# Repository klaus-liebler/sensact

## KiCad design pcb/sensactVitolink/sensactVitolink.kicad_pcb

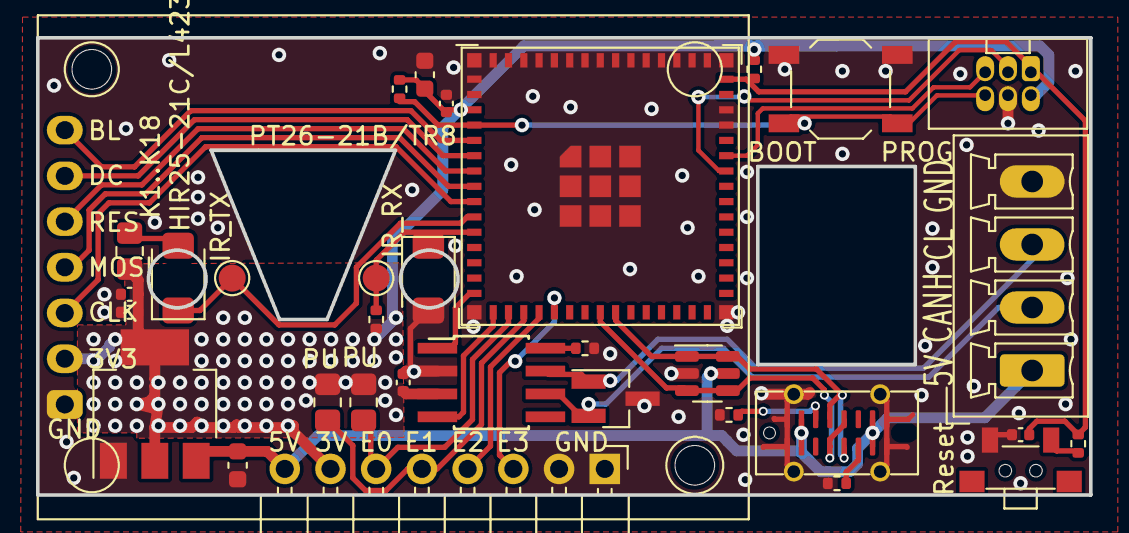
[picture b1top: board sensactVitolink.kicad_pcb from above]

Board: 2 copper layers, 58.5 x 25.4 mm, 35 parts (0 on the bottom side), 29 nets.

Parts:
C1, C2, C3, C8: u1; C_0402_1005Metric
C4: 22u; C_0603_1608Metric
C7: 10u; C_0603_1608Metric
C9: 10u; C_0402_1005Metric
D1: HIR25-21C/L423/2T; LED_1206_3216Metric_ReverseMount_Hole1.8x2.4mm
D2: NUP2105; SOT-23_Handsoldering
H1, H2: MountingHole; MountingHole_2.2mm_M2
J1: PROG; IDC_2x03_P1.27mm_Vertical
J2: Ext; PinHeader_1x08_P2.54mm_Horizontal
J3: 5V CL CH GN; PhoenixContact_MCV_1,5_4-G-3.5_1x04_P3.50mm_Vertical
J4: USB; GT-USB-7051A
Q1: PT26-21B/TR8; LED_1206_3216Metric_ReverseMount_Hole1.8x2.4mm
R1: 4k7; R_0402_1005Metric
R2, R10: 5k1; R_0402_1005Metric
R3, R4: PU; R_0805_2012Metric_Pad1.20x1.40mm_HandSolder
R5: K1..K18; R_0805_2012Metric_Pad1.20x1.40mm_HandSolder
R6, R8, R9: 10k; R_0402_1005Metric
R7: k1; R_0402_1005Metric
SW2: Reset; Button_2x4x3,5_handsolder
SW3: BOOT; SW_SPST_TL3342
TP1: IR_TX; TestPoint_Pad_D1.5mm
TP2: IR_RX; TestPoint_Pad_D1.5mm
U1: ESP32-S3-MINI-1; ESP32-S3-MINI-1U
U2: AMS1117-3.3; SOT-223-3_TabPin2
U3: SRV05-4; SOT-23-6
U4: SN65HVD230; SOIC-8_3.9x4.9mm_Pitch1.27mm_handsolder
U5: IPS_240_240; IPS_240_240_1.3

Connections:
+3V3: C1.1, C2.1, C4.1, C8.1, C9.1, J1.2, J2.7, R3.1, R4.1, R5.1, R6.1, R8.2, R9.2, U1.3 (3V3), U2.2 (VO), U4.3 (VCC), U5.2 (VCC)
+5V: C7.1, J2.8, J3.1, J4.A4 (VBUS), J4.A9 (VBUS), J4.B4 (VBUS), J4.B9 (VBUS), U2.3 (VI), U3.5 (VP)
/USB+: J4.A6 (D+), J4.B6 (D+), U1.24 (GPIO20/U1CTS/ADC2_CH9/CLK_OUT1/USB_D+), U3.1 (IO1), U3.6 (IO4)
/USB-: J4.A7 (D-), J4.B7 (D-), U1.23 (GPIO19/U1RTS/ADC2_CH8/CLK_OUT2/USB_D-), U3.3 (IO2), U3.4 (IO3)
CANH: D2.1 (A1), J3.3, U4.7 (CANH)
CANL: D2.2 (A2), J3.2, U4.6 (CANL)
CAN_RX: U1.16 (GPIO12/TOUCH12/ADC2_CH1/FSPICLK/FSPIIO6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), U4.4 (R)
CAN_TX: U1.15 (GPIO11/TOUCH11/ADC2_CH0/FSPID/FSPIIO5/S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), U4.1 (D)
EXT0: J2.6, R3.2, U1.17 (GPIO13/TOUCH13/ADC2_CH2/FSPIQ/FSPIIO7/S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)
EXT1: J2.5, R4.2, U1.18 (GPIO14/TOUCH14/ADC2_CH3/FSPIWP/FSPIDQS/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)
EXT2: J2.4, U1.19 (GPIO15/U0RTS/ADC2_CH4/XTAL_32K_P)
EXT3: J2.3, U1.20 (GPIO16/U0CTS/ADC2_CH5/XTAL_32K_NH5)
GND: C1.2, C2.2, C3.2, C4.2, C7.2, C8.2, C9.2, D2.3 (common), J1.4, J2.1, J2.2, J3.4, J4.A1 (GND), J4.A12 (GND), J4.B1 (GND), J4.B12 (GND), J4.S1 (SHIELD), Q1.2 (E), R1.2, R2.2, R10.2, SW2.2, SW3.1, U1.1 (GND), U1.2 (GND), U1.42 (GND), U1.43 (GND), U1.46 (GND), U1.47 (GND), U1.48 (GND), U1.49 (GND), U1.50 (GND), U1.51 (GND), U1.52 (GND), U1.53 (GND), U1.54 (GND), U1.55 (GND), U1.56 (GND), U1.57 (GND), U1.58 (GND), U1.59 (GND), U1.60 (GND), U1.61 (GND), U1.62 (GND), U1.63 (GND), U1.64 (GND), U1.65 (GND), U2.1 (GND), U3.2 (VN), U4.2 (GND), U5.1 (GND)
IR_LED: D1.1 (K), TP1.1, U1.10 (GPIO6/TOUCH6/ADC1_CH5)
IR_TRANS: Q1.1 (C), R6.2, TP2.1, U1.11 (GPIO7/TOUCH7/ADC1_CH6)
LCD_BACKLIGHT: U1.5 (GPIO1/TOUCH1/ADC1_CH0), U5.7 (BLK)
LCD_CLK: U1.9 (GPIO5/TOUCH5/ADC1_CH4), U5.3 (SCL)
LCD_DC: U1.6 (GPIO2/TOUCH2/ADC1_CH1), U5.6 (DVC)
LCD_MOSI: U1.8 (GPIO4/TOUCH4/ADC1_CH3), U5.4 (SDA)
LCD_RES: U1.7 (GPIO3/TOUCH3/ADC1_CH2), U5.5 (RES)
unnamed: D1.2 (A), R5.2
unnamed: J4.A5 (CC1), R2.1
unnamed: J4.B5 (CC2), R10.1
unnamed: R7.1, SW2.1
unnamed: R1.1, U4.8 (Rs)
PROG_EN: C3.1, J1.1, R7.2, R8.1, U1.45 (EN)
PROG_IO0: J1.6, R9.1, SW3.2, U1.4 (GPIO0/BOOT)
PROG_RX: J1.5, U1.40 (U0RXD/GPIO44/CLK_OUT2)
PROG_TX: J1.3, U1.39 (U0TXD/GPIO43/CLK_OUT1)

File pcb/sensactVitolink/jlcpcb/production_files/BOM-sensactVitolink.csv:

Comment,Designator,Footprint,LCSC
PT26-21B/TR8,Q1,LED_1206_3216Metric_ReverseMount_Hole1.8x2.4mm,C131248
u1,"C1,C2,C3,C8",C_0402_1005Metric,C1525
10u,C9,C_0402_1005Metric,C15525
10u,C7,C_0603_1608Metric,C19702
k1,R7,R_0402_1005Metric,C25076
10k,"R6,R8,R9",R_0402_1005Metric,C25744
4k7,R1,R_0402_1005Metric,C25900
5k1,"R10,R2",R_0402_1005Metric,C25905
HIR25-21C/L423/2T,D1,LED_1206_3216Metric_ReverseMount_Hole1.8x2.4mm,C282224
USB,J4,GT-USB-7051A,C2843970
ESP32-S3-MINI-1,U1,ESP32-S3-MINI-1U,C2980299
BOOT,SW3,SW_SPST_TL3342,C318884
22u,C4,C_0603_1608Metric,C59461
AMS1117-3.3,U2,SOT-223-3_TabPin2,C6186
SRV05-4,U3,SOT-23-6,C85364
K1..K18,R5,R_0805_2012Metric_Pad1.20x1.40mm_HandSolder,
IR_TX,TP1,TestPoint_Pad_D1.5mm,
PROG,J1,IDC_2x03_P1.27mm_Vertical,
NUP2105,D2,SOT-23_Handsoldering,
Reset,SW2,"Button_2x4x3,5_handsolder",
SN65HVD230,U4,SOIC-8_3.9x4.9mm_Pitch1.27mm_handsolder,
5V CL CH GN,J3,"PhoenixContact_MCV_1,5_4-G-3.5_1x04_P3.50mm_Vertical",
MountingHole,H1,MountingHole_2.2mm_M2,
Ext,J2,PinHeader_1x08_P2.54mm_Horizontal,
IR_RX,TP2,TestPoint_Pad_D1.5mm,
PU,R4,R_0805_2012Metric_Pad1.20x1.40mm_HandSolder,
MountingHole,H2,MountingHole_2.2mm_M2,
IPS_240_240,U5,IPS_240_240_1.3,
PU,R3,R_0805_2012Metric_Pad1.20x1.40mm_HandSolder,

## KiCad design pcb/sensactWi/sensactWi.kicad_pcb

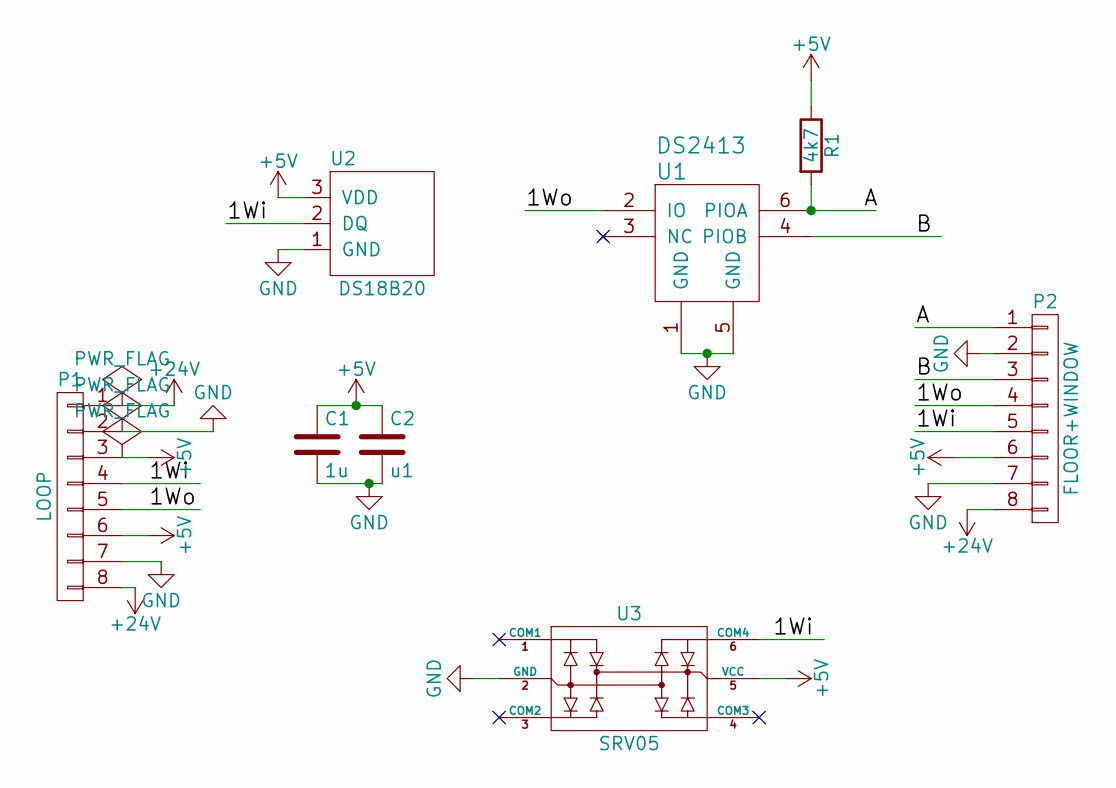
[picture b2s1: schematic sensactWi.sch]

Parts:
C1: 1u; C_0805_HandSoldering
C2: u1; C_0805_HandSoldering
P1: LOOP; KF141R-8p
P2: FLOOR+WINDOW; KF141R-8p
R1: 4k7; R_0805_HandSoldering
U1: DS2413; TSOC6
U2: DS18B20; TO-92_Horizontal1_Inline_Narrow_Oval
U3: SRV05; SOT-23-6_handsolder

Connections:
+5V: C1.1, C2.1, P1.3, P1.6, P2.6, R1.1, U2.3 (VDD), U3.5 (VCC)
+24V: P1.1, P1.8, P2.8
/1Wi: P1.4, P2.5, U2.2 (DQ), U3.6 (COM4)
/1Wo: P1.5, P2.4, U1.2 (IO)
/A: P2.1, R1.2, U1.6 (PIOA)
/B: P2.3, U1.4 (PIOB)
GND: C1.2, C2.2, P1.2, P1.7, P2.2, P2.7, U1.1 (GND), U1.5 (GND), U2.1 (GND), U3.2 (GND)

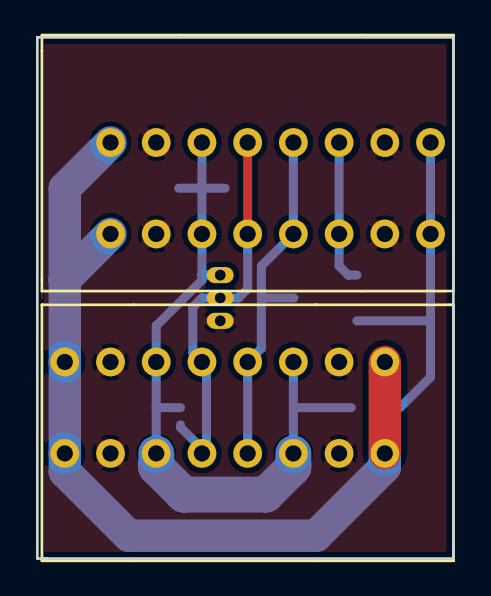
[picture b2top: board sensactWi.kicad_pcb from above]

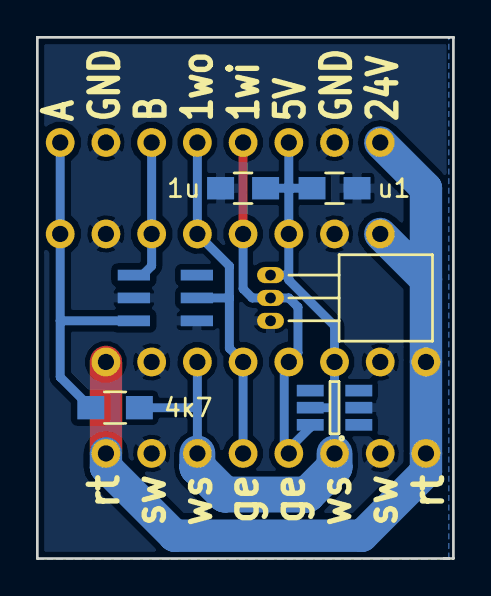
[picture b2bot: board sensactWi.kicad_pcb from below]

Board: 2 copper layers, 23.1 x 29.0 mm, 8 parts (6 on the bottom side), 7 nets.

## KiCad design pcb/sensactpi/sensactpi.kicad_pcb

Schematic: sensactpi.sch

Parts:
C1, C2, C8: 22p; C_0805_HandSoldering
C3, C5, C7, C9, C55, C57: u1; C_0805_HandSoldering
C4, C6, C56: 10u; C_1206_HandSoldering
JP1: CANR; SMD-solder-bridge-3pin
JP2: CANT; SMD-solder-bridge-3pin
JP3: WP; SMD-solder-bridge
JP4: CAN_TERM; Pin_Header_Straight_1x02_Pitch2.54mm
P1: 24V; conn_2P
P2: IN_OUT; KF141R-8p
P3: BUS1; IDC-Header_2x05_Pitch2.54mm_Angled
P7: CONN_02X10; IDC-Header_2x10_Pitch2.54mm_Straight
P8: SI7021-1; MODULE_SI7021
P11: SI7021-2; MODULE_SI7021
R1, R7, R10: 10k; R_0805_HandSoldering
R2, R3, R5, R22, R23: 1k; R_0805_HandSoldering
R8, R20: 4k7; R_0805_HandSoldering
R9: 120R; R_1206_HandSoldering
SW1: ROTARY_ENCODER_SWITCH; encoder_alps-ec12d_case
U1: MODULE_ST7735_1_8; MODULE_ST7735_18
U2: PCA9685; TSSOP-28_4.4x9.7mm_Pitch0.65mm_handsolder
U3: DS2482; SOIC-8_3.9x4.9mm_Pitch1.27mm_handsolder
U4: MCP2515-I/ST; TSSOP-20_4.4x6.5mm_Pitch0.65mm_handsolder
U5: 24LC16; SOIC-8_3.9x4.9mm_Pitch1.27mm_handsolder
U6: SN65HVD230; SOIC-8_3.9x4.9mm_Pitch1.27mm_handsolder
U7: TJA1021T; SOIC-8_3.9x4.9mm_Pitch1.27mm_handsolder
Y1: 8MHz; quartz3225

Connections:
+3V3: C3.1, C4.2, C5.2, C6.1, C7.1, C55.1, C56.1, C57.1, P3.1, P8.1, P11.1, R1.2, R2.1, R3.1, R5.1, R8.1, R10.1, R20.1, R22.1, R23.2, U1.1, U2.28, U3.1, U4.20 (VDD), U5.8, U6.3; also elsewhere on the board
+24V: C9.1, P1.1, P2.4, P2.5, P3.7, P3.8, U7.7 (VBAT); also elsewhere on the board
/LED0: P7.20, U2.6
/LED1: P7.19, U2.7
/LED2: P7.18, U2.8
/LED3: P7.17, U2.9
/LED4: P7.16, U2.10
/LED5: P7.15, U2.11
/LED6: P7.14, U2.12
/LED7: P7.13, U2.13
/LED8: P7.5, U2.15
/LED9: P7.6, U2.16
/LED10: P7.7, U2.17
/LED11: P7.8, U2.18
/LED12: P7.9, U2.19
/LED13: P7.10, U2.20
/LED14: P7.11, U2.21
/LED15: P7.12, U2.22
/RXCAN: JP1.1, U4.2 (RXCAN)
/RXD: JP1.2, U6.4
/TXCAN: JP2.1, U4.1 (TXCAN)
/TXD: JP2.2, U6.1
CANH: JP4.1, P2.3, P2.6, U6.7
CANL: P2.2, P2.7, R9.1, U6.6
CANR: JP1.3; also elsewhere on the board
CANT: JP2.3; also elsewhere on the board
CAN_CS: U4.18 (~CS); also elsewhere on the board
CAN_INT: U4.13 (~INT); also elsewhere on the board
CAN_SCK: U1.7, U4.14 (SCK); also elsewhere on the board
CAN_SI: U1.6, U4.16 (SI); also elsewhere on the board
CAN_SO: U4.17 (SO); also elsewhere on the board
ENC_A: R22.2, SW1.1; also elsewhere on the board
ENC_B: R23.1, SW1.3; also elsewhere on the board
ENC_SW: SW1.5; also elsewhere on the board
GND: C1.2, C2.2, C3.2, C4.1, C5.1, C6.2, C7.2, C8.2, C9.2, C55.2, C56.2, C57.2, JP3.2, P1.2, P2.1, P2.8, P3.9, P3.10, P8.2, P11.2, R7.1, SW1.2, SW1.4, SW1.6, U1.2, U2.1, U2.2, U2.3, U2.4, U2.5, U2.14, U2.23, U2.24, U3.3, U3.7, U3.8, U4.10 (VSS), U5.1, U5.2, U5.3, U5.4, U6.2, U7.5 (GND), Y1.2, Y1.4; also elsewhere on the board
ID_SC: U5.6; also elsewhere on the board
ID_SD: U5.5; also elsewhere on the board
INT1_1: P3.4; also elsewhere on the board
INT1_2: P3.5; also elsewhere on the board
INT1_3: P3.6; also elsewhere on the board
LCD_CS: U1.3; also elsewhere on the board
LCD_DC: U1.5; also elsewhere on the board
LCD_PWM: U1.8; also elsewhere on the board
LCD_RES: U1.4; also elsewhere on the board
LIN: C8.1, U7.6 (LIN)
LINRX: R10.2, U7.4 (RXD); also elsewhere on the board
LINTX: U7.1 (TXD); also elsewhere on the board
unnamed: C1.1, U4.8 (OSC2), Y1.1
unnamed: C2.1, U4.9 (OSC1), Y1.3
unnamed: JP3.1, R2.2, U5.7
unnamed: JP4.2, R9.2
unnamed: R1.1, U4.19 (~RESET)
unnamed: R7.2, U6.8
SCL1: P3.2, P8.3, R5.2, U3.4; also elsewhere on the board
SCL2: P11.3, R20.2, U2.26; also elsewhere on the board
SDA1: P3.3, P8.4, R3.2, U3.5; also elsewhere on the board
SDA2: P11.4, R8.2, U2.27; also elsewhere on the board
SHDN: U7.2 (~SLP~); also elsewhere on the board

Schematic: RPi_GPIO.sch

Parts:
D4: LED; LED_0805_handsolder
J1: RPi_GPIO; Pin_Header_Straight_2x20_Pitch2.54mm
R21: k22; R_0805_HandSoldering

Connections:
+5V: J1.2, J1.4; also elsewhere on the board
AUDIO_BCK: J1.12; also elsewhere on the board
AUDIO_DATA: J1.40; also elsewhere on the board
AUDIO_LCK: J1.35; also elsewhere on the board
BOOT0: J1.29; also elsewhere on the board
CAN_CS: J1.26; also elsewhere on the board
CAN_INT: J1.16; also elsewhere on the board
CAN_SCK: J1.23; also elsewhere on the board
CAN_SI: J1.19; also elsewhere on the board
CAN_SO: J1.21; also elsewhere on the board
GND: J1.6, J1.9, J1.14, J1.20, J1.25, J1.30, J1.34, J1.39; also elsewhere on the board
ID_SC: J1.28; also elsewhere on the board
ID_SD: J1.27; also elsewhere on the board
INT1_1: J1.7; also elsewhere on the board
INT1_2: J1.11; also elsewhere on the board
INT1_3: J1.13; also elsewhere on the board
LCD_CS: J1.24; also elsewhere on the board
LCD_DC: J1.36; also elsewhere on the board
LCD_PWM: J1.37; also elsewhere on the board
LCD_RES: J1.33; also elsewhere on the board
NRST: J1.22; also elsewhere on the board
unnamed: D4.1, R21.1
unnamed: D4.2, J1.17
RX: J1.8; also elsewhere on the board
SCL1: J1.3; also elsewhere on the board
SDA1: J1.5; also elsewhere on the board
SHUTDOWN: J1.32; also elsewhere on the board
TX: J1.10; also elsewhere on the board

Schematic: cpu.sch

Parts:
C10: 4u7; C_1206_HandSoldering
C11, C12, C13: u1; C_0805_HandSoldering
C14: 10n; C_0805_HandSoldering
C15: 1u; C_0805_HandSoldering
C51, C52: 22p; C_0805_HandSoldering
D1: LED; LED_0805_handsolder
P4: CONN_01X06; MicroUsbVertical
P5: USB; MicroUsbVertical
P9: CPU_IO; Pin_Header_Straight_1x03_Pitch2.54mm
P10: CONN_01X05; Pin_Header_Straight_1x05_Pitch2.00mm
P12: CONN_01X03; Pin_Header_Straight_1x03_Pitch2.00mm
P13: EXT; Pin_Header_Straight_1x04_Pitch1.27mm
R4, R11: k22; R_0805_HandSoldering
R6: M1; R_0805_HandSoldering
U8: STM32F072C8Tx; LQFP-48_7x7mm_Pitch0.5mm_handsolder
Y2: 8MHz; quartz3225

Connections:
+3V3: C10.1, C11.1, C12.1, C13.1, C14.1, C15.1, P10.3, R11.2, U8.1, U8.9, U8.24, U8.36, U8.48; also elsewhere on the board
/cpu/LED: D1.2, R11.1
/cpu/USBM: P5.2, U8.32
/cpu/USBP: P5.3, U8.33
BOOT0: U8.44; also elsewhere on the board
CANR: U8.45; also elsewhere on the board
CANT: U8.46; also elsewhere on the board
DBG_RX: P4.5, U8.22
DBG_TX: P4.4, U8.21
ENC_A: P9.2, U8.39; also elsewhere on the board
ENC_B: P9.1, U8.38; also elsewhere on the board
ENC_SW: P9.3, U8.40; also elsewhere on the board
GND: C10.2, C11.2, C12.2, C13.2, C14.2, C15.2, C51.2, C52.2, P4.2, P4.6, P5.5, P5.6, P10.4, P10.5, R6.2, U8.8, U8.23, U8.35, U8.47, Y2.2, Y2.4; also elsewhere on the board
LINRX: U8.13; also elsewhere on the board
LINTX: U8.12; also elsewhere on the board
NRST: U8.7; also elsewhere on the board
unnamed: C51.1, U8.5, Y2.3
unnamed: C52.1, R4.2, Y2.1
unnamed: D1.1, U8.20
unnamed: P5.4, R6.1
unnamed: P13.1, U8.17
unnamed: P13.2, U8.16
unnamed: P13.3, U8.15
unnamed: P13.4, U8.14
unnamed: R4.1, U8.6
PB12: P12.3, U8.25
PB13: P10.2, U8.26
PB14: P12.2, U8.27
PB15: P12.1, U8.28
RX: U8.31; also elsewhere on the board
SCL2: U8.42; also elsewhere on the board
SDA2: U8.43; also elsewhere on the board
SHDN: U8.11; also elsewhere on the board
SWCLK: P4.1, U8.37
SWDIO: P4.3, U8.34
TX: U8.30; also elsewhere on the board
WS2812: P10.1, U8.29

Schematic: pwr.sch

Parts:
C16, C17: 10n; C_0805_HandSoldering
C18, C19, C20, C21: 4u7; C_1206_HandSoldering
C22, C23, C24, C25: m1; C_1206_HandSoldering
D2, D3: D_Schottky; do214aa_handsolder
L2: 47u; Inductor_CD104_handsolder
L3: 22u; Inductor_CD104_handsolder
R12, R13: 10k; R_0805_HandSoldering
R14: 3K3; R_0805_HandSoldering
R15: 1k5; R_0805_HandSoldering
R16: 6k8; R_0805_HandSoldering
U9, U10: TPS5430; SOIC-8_3.9x4.9mm_Pitch1.27mm_pad_handsolder

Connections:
+3V3: C23.1, C25.1, L2.1, R13.1; also elsewhere on the board
+5V: C22.1, C24.1, L3.1, R12.1; also elsewhere on the board
+24V: C18.1, C19.1, C20.1, C21.1, U9.7, U10.7; also elsewhere on the board
/pwr/BOOT3V3: C17.2, U10.1
/pwr/BOOT5V: C16.2, U9.1
/pwr/SW3V3: C17.1, D3.1, L2.2, U10.8
/pwr/SW5V: C16.1, D2.1, L3.2, U9.8
GND: C18.2, C19.2, C20.2, C21.2, C22.2, C23.2, C24.2, C25.2, D2.2, D3.2, R14.2, R16.1, U9.2, U9.3, U9.6, U9.9, U10.2, U10.3, U10.6, U10.9; also elsewhere on the board
unnamed: R12.2, R14.1, U9.4
unnamed: R13.2, R15.1
unnamed: R15.2, R16.2, U10.4

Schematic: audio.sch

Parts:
C26, C29, C33, C35: 10u; C_1206_HandSoldering
C27, C31, C32, C34, C44: u1; C_0805_HandSoldering
C28, C30: 2u2; C_0805_HandSoldering
C36, C37, C38, C39: 1u; C_0805_HandSoldering
C40: m1; CP_Radial_D8.0mm_P3.50mm
C41, C42, C43, C45: u22; C_0805_HandSoldering
C46, C47, C48, C49, C50: 1n; C_0805_HandSoldering
L4, L5, L6, L7, L8: FB; C_1206_HandSoldering
P6: AUDIO OUT; JST_XH_S04B-XH-A_04x2.50mm_Angled
R17: 10R; R_0805_HandSoldering
R18: 1k; R_0805_HandSoldering
R19: M1; R_0805_HandSoldering
TP1: R; Measurement_Point_Round-SMD-Pad_Small
TP2: L; Measurement_Point_Round-SMD-Pad_Small
U11: PCM5102A; TSSOP-20_4.4x6.5mm_Pitch0.65mm_handsolder
U12: TPA3110D2; TSSOP-28_4.4x9.7mm_Pitch0.65mm_pad_handsolder

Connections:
+3.3VA: C26.1, C27.1, C29.1, C31.1, L8.1, U11.1, U11.8
+3V3: C32.1, C33.1, L8.2, U11.17, U11.20; also elsewhere on the board
+24V: C40.1, C44.1, C46.1, R17.2, R19.1, U12.15, U12.16, U12.27, U12.28; also elsewhere on the board
/audio/BSNL: C42.2, U12.22
/audio/BSNR: C45.2, U12.21
/audio/BSPL: C41.2, U12.26
/audio/BSPR: C43.2, U12.17
/audio/OUTL: TP2.1, U11.6, U12.3
/audio/OUTNL: C42.1, L6.2, U12.23
/audio/OUTNR: C45.1, L7.2, U12.20
/audio/OUTPL: C41.1, L4.2, U12.25
/audio/OUTPR: C43.1, L5.2, U12.18
/audio/OUTR: TP1.1, U11.7, U12.12
/audio/OUT_L+: C49.1, L4.1, P6.4
/audio/OUT_L-: C47.2, L6.1, P6.3
/audio/OUT_R+: C50.2, L5.1, P6.1
/audio/OUT_R-: C48.1, L7.1, P6.2
AUDIO_BCK: U11.13; also elsewhere on the board
AUDIO_DATA: U11.14; also elsewhere on the board
AUDIO_LCK: U11.15; also elsewhere on the board
GND: C26.2, C27.2, C28.1, C29.2, C31.2, C32.2, C33.2, C34.1, C35.1, C36.2, C37.2, C38.2, C39.1, C40.2, C44.2, C46.2, C47.1, C48.2, C49.2, C50.1, U11.3, U11.9, U11.10, U11.11, U11.12, U11.16, U11.19, U12.5, U12.6, U12.8, U12.14, U12.19, U12.24, U12.29; also elsewhere on the board
unnamed: C28.2, U11.5
unnamed: C30.1, U11.2
unnamed: C30.2, U11.4
unnamed: C34.2, C35.2, U11.18
unnamed: C36.1, R17.1, U12.7
unnamed: C37.1, U12.11
unnamed: C38.1, U12.4
unnamed: C39.2, U12.9, U12.10
unnamed: R18.1, R19.2, U12.1
SHUTDOWN: R18.2; also elsewhere on the board

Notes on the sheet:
SCK->GND = INSIDE PLL!

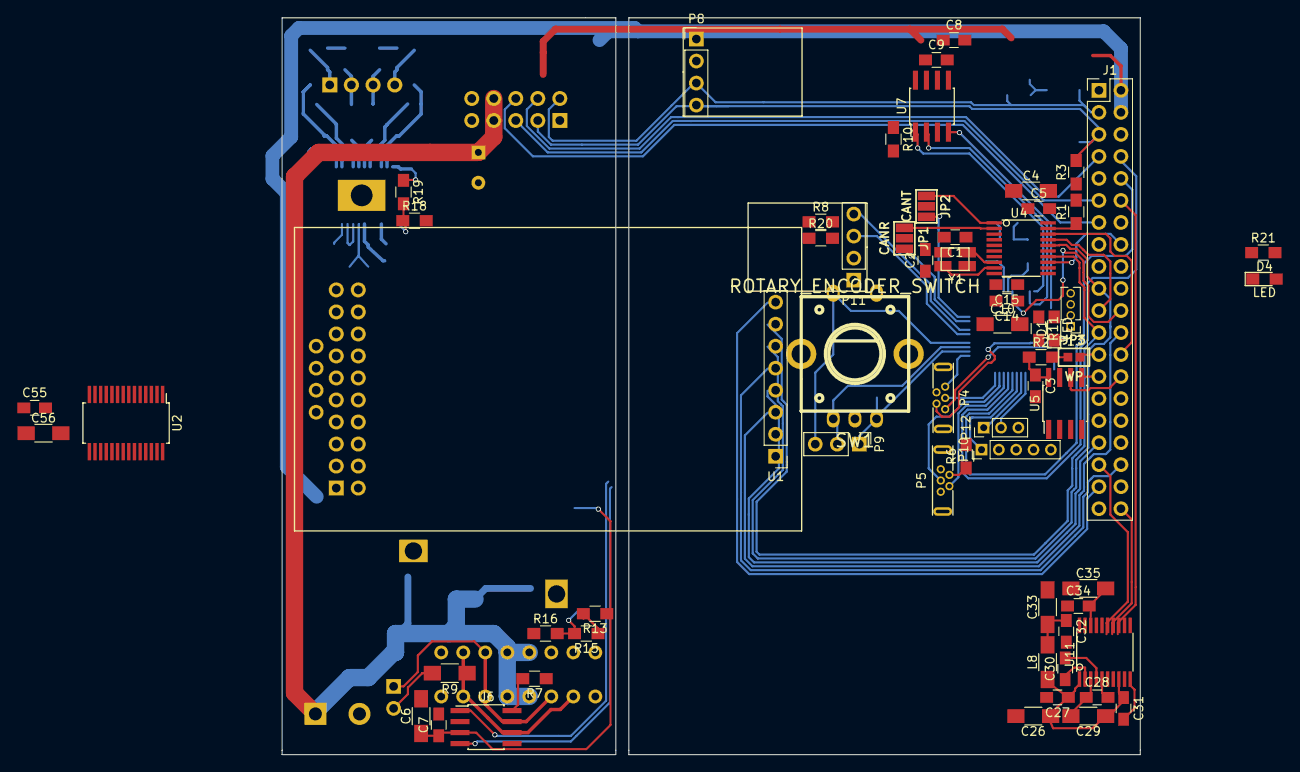
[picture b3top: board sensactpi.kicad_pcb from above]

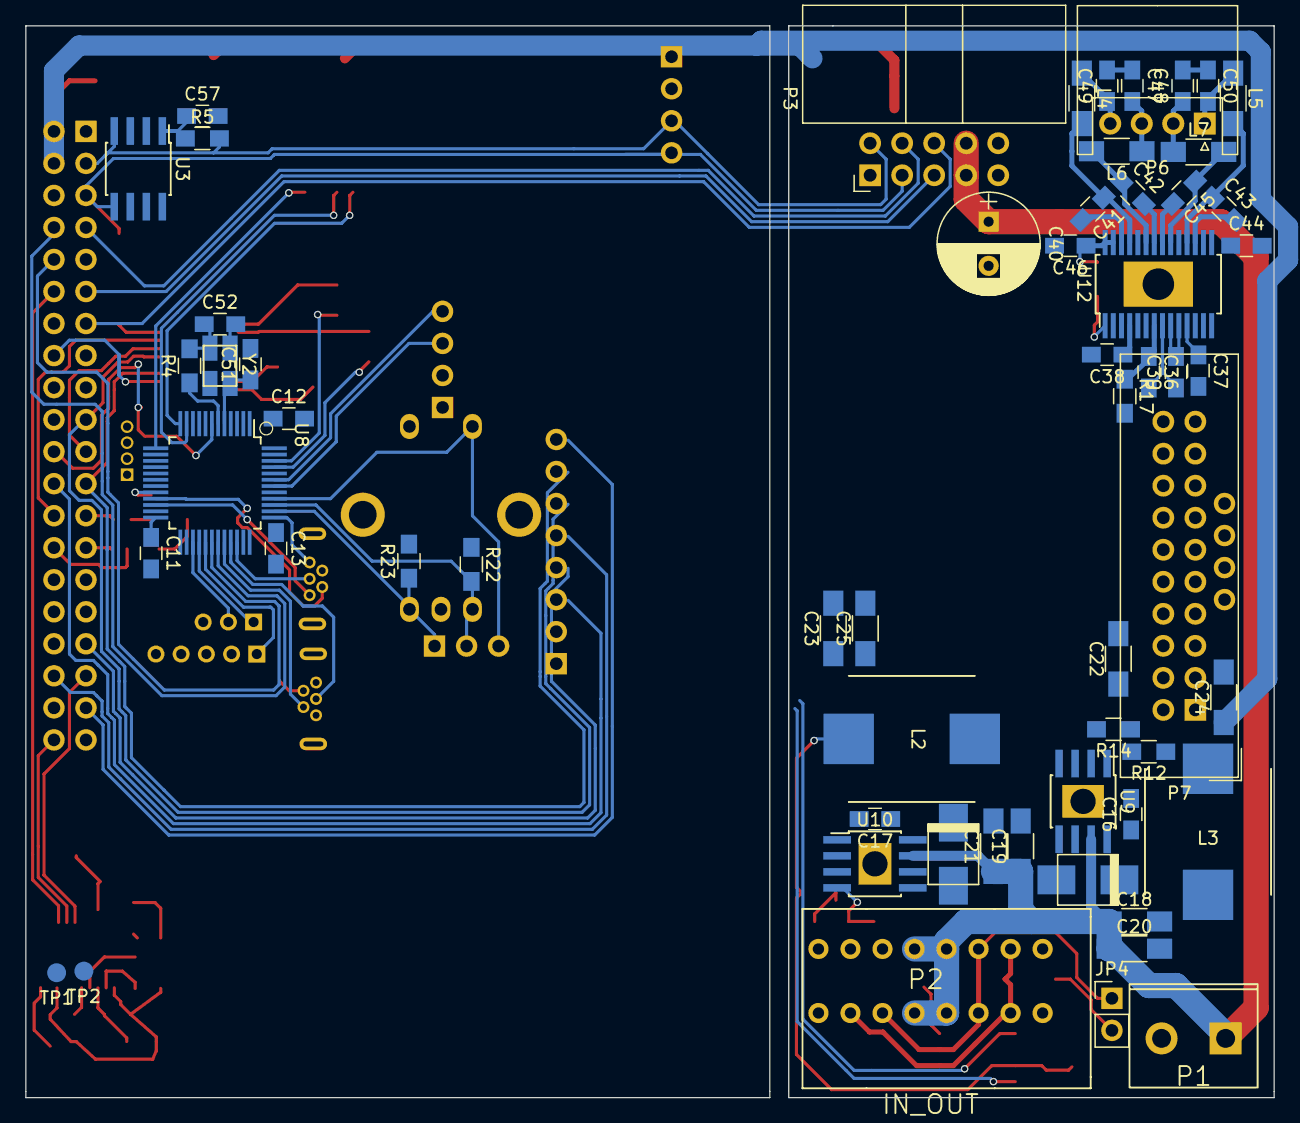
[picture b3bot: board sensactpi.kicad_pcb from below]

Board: 2 copper layers, 99.0 x 85.0 mm, 124 parts (60 on the bottom side), 121 nets.
